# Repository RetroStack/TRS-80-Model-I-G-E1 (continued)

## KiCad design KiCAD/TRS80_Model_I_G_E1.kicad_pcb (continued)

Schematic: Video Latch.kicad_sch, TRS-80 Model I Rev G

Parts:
R39: 4.7k; TRS80_Model_I_R_0.25W
Z7: 74LS74; TRS80_Model_I_DIP14
Z27: 74LS175; TRS80_Model_I_DIP16
Z28: 74LS174; TRS80_Model_I_DIP16
Z30: 74LS02; TRS80_Model_I_DIP14
Z42: 74LS04; TRS80_Model_I_DIP14

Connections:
+5V: R39.2, Z7.14 (VCC), Z27.16 (VCC), Z28.16 (VCC); also elsewhere on the board
/Address Decoder/~VID: Z7.4 (~S); also elsewhere on the board
/Video/Video Counter/HDRV: Z30.8; also elsewhere on the board
/Video/Video Counter/L3: Z27.12 (D2); also elsewhere on the board
/Video/Video Counter/VDRV: Z30.9; also elsewhere on the board
/Video/Video Counter/~LATCH: Z7.3 (C), Z27.9 (Cp), Z28.9 (Cp); also elsewhere on the board
/Video/Video Generator/GRAPHICS: Z27.3 (~Q0); also elsewhere on the board
/Video/Video Generator/LB0: Z28.15 (Q5); also elsewhere on the board
/Video/Video Generator/LB1: Z28.12 (Q4); also elsewhere on the board
/Video/Video Generator/LB2: Z28.2 (Q0); also elsewhere on the board
/Video/Video Generator/LB3: Z28.7 (Q2); also elsewhere on the board
/Video/Video Generator/LB4: Z28.5 (Q1); also elsewhere on the board
/Video/Video Generator/LB5: Z28.10 (Q3); also elsewhere on the board
/Video/Video Generator/LB6: Z27.15 (Q3); also elsewhere on the board
/Video/Video Generator/~BLANK: Z27.7 (Q1); also elsewhere on the board
/Video/Video Generator/~CHARGAP: Z27.11 (~Q2); also elsewhere on the board
/Video/Video Generator/~GRAPHICS: Z27.2 (Q0); also elsewhere on the board
/Video/Video Latch/VD0: Z28.14 (D5); also elsewhere on the board
/Video/Video Latch/VD1: Z28.13 (D4); also elsewhere on the board
/Video/Video Latch/VD2: Z28.3 (D0); also elsewhere on the board
/Video/Video Latch/VD3: Z28.6 (D2); also elsewhere on the board
/Video/Video Latch/VD4: Z28.4 (D1); also elsewhere on the board
/Video/Video Latch/VD5: Z28.11 (D3); also elsewhere on the board
/Video/Video Latch/VD6: Z27.13 (D3); also elsewhere on the board
/Video/Video Latch/VD7: Z42.13; also elsewhere on the board
/Video/Video Latch/~VCLR: Z7.6 (~Q), Z27.1 (~Mr), Z28.1 (~Mr)
GND: Z7.2 (D), Z7.7 (GND), Z7.10 (~S), Z7.11 (C), Z7.12 (D), Z7.13 (~R), Z27.8 (GND), Z28.8 (GND); also elsewhere on the board
unnamed: R39.1, Z7.1 (~R)
unnamed: Z27.4 (D0), Z42.12
unnamed: Z27.5 (D1), Z30.10

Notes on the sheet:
CHARGAP
GRAPHICS
Clear when CPU drives
~{BLANK}
~{GRAPHICS}

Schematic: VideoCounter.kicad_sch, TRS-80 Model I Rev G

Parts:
R63: 4.7k; TRS80_Model_I_R_0.25W
Z12, Z32, Z50, Z65: 74LS93; TRS80_Model_I_DIP14
Z24: 74LS132; TRS80_Model_I_DIP14
Z43: 74LS157; TRS80_Model_I_DIP16
Z58: 74LS92; TRS80_Model_I_DIP14
Z66: 74LS11; TRS80_Model_I_DIP14
Z70: 74LS74; TRS80_Model_I_DIP14

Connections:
+5V: R63.1, Z12.5 (VCC), Z32.5 (VCC), Z43.16 (VCC), Z50.5 (VCC), Z58.5 (VCC), Z65.5 (VCC), Z66.14 (VCC); also elsewhere on the board
/CPU/CLK: Z43.3 (I1a), Z70.11 (C); also elsewhere on the board
/CPU/HI: Z70.10 (~S); also elsewhere on the board
/CPU/~CLK_EN: Z58.6 (R0(1)), Z58.7 (R0(2)); also elsewhere on the board
/Cassette Interface/MODESEL: Z43.1 (S); also elsewhere on the board
/Video/Video Access Multiplexer/C0: Z43.7 (Zb); also elsewhere on the board
/Video/Video Access Multiplexer/C1: Z65.9 (Q1); also elsewhere on the board
/Video/Video Access Multiplexer/C2: Z50.14 (CP0), Z65.8 (Q2); also elsewhere on the board
/Video/Video Access Multiplexer/C3: Z50.1 (CP1..3), Z50.12 (Q0); also elsewhere on the board
/Video/Video Access Multiplexer/C4: Z50.9 (Q1), Z66.3; also elsewhere on the board
/Video/Video Access Multiplexer/C5: Z50.8 (Q2), Z66.5; also elsewhere on the board
/Video/Video Access Multiplexer/R0: Z32.14 (CP0), Z65.12 (Q0); also elsewhere on the board
/Video/Video Access Multiplexer/R1: Z32.1 (CP1..3), Z32.12 (Q0), Z66.13; also elsewhere on the board
/Video/Video Access Multiplexer/R2: Z32.9 (Q1), Z66.2; also elsewhere on the board
/Video/Video Access Multiplexer/R3: Z32.8 (Q2); also elsewhere on the board
/Video/Video Counter/HDRV: Z12.14 (CP0), Z50.11 (Q3), Z66.4; also elsewhere on the board
/Video/Video Counter/L0: Z12.1 (CP1..3), Z12.12 (Q0); also elsewhere on the board
/Video/Video Counter/L1: Z12.9 (Q1); also elsewhere on the board
/Video/Video Counter/L2: Z12.8 (Q2), Z66.9, Z66.10; also elsewhere on the board
/Video/Video Counter/L3: Z12.11 (Q3), Z65.14 (CP0), Z66.11; also elsewhere on the board
/Video/Video Counter/SHIFT: Z43.4 (Za), Z58.14 (CP0); also elsewhere on the board
/Video/Video Counter/VDRV: Z32.11 (Q3), Z66.1; also elsewhere on the board
/Video/Video Counter/~LATCH: Z24.3; also elsewhere on the board
GND: Z12.10 (GND), Z32.10 (GND), Z43.5 (I0b), Z43.8 (GND), Z43.15 (E), Z50.10 (GND), Z58.10 (GND), Z65.2 (R0(1)), Z65.3 (R0(2)), Z65.10 (GND), Z66.7 (GND); also elsewhere on the board
unnamed: Z12.2 (R0(1)), Z12.3 (R0(2)), Z66.8
unnamed: Z32.2 (R0(1)), Z32.3 (R0(2)), Z66.12
unnamed: Z43.2 (I0a), Z70.9 (Q)
unnamed: Z24.2, Z43.11 (I0c), Z58.9 (Q2)
unnamed: Z43.6 (I1b), Z43.10 (I1c), Z58.8 (Q3)
unnamed: Z43.9 (Zc), Z65.1 (CP1..3)
unnamed: Z50.2 (R0(1)), Z50.3 (R0(2)), Z66.6
unnamed: Z24.1, Z58.1 (CP1..3), Z58.12 (Q0)
unnamed: Z70.8 (~Q), Z70.12 (D)
unnamed: R63.2, Z70.13 (~R)

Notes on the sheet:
BIT 1
7.92 kHz
CLK/2
660 Hz
CP0/2
1.98 kHz
60 Hz
887.042 kHz
1.32 kHz
Character line counter
82.5 Hz
27.72 kHz
Mode Selector
CP0/11
3.96 kHz
110.88 kHz
CP1/4
221.76 kHz
55.44 kHz
15.84 kHz
CP0/6
CP0/12
BIT 3
330 Hz
Column counter
Row counter
10.6445 MHz
5.322 MHz
443.52 kHz
CP0/14
165 Hz
Every 6th count

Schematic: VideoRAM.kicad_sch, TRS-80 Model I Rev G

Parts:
Z30: 74LS02; TRS80_Model_I_DIP14
Z44, Z60: 74LS367; TRS80_Model_I_DIP16
Z45, Z46, Z47, Z48, Z61, Z62, Z63: 2102; DIP-16_W7.62mm

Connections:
+5V: Z45.10 (VCC), Z46.10 (VCC), Z47.10 (VCC), Z48.10 (VCC), Z60.16 (VCC), Z61.10 (VCC), Z62.10 (VCC), Z63.10 (VCC); also elsewhere on the board
/D0: Z44.7, Z48.11 (IN); also elsewhere on the board
/D1: Z44.5, Z47.11 (IN); also elsewhere on the board
/D2: Z44.3, Z46.11 (IN); also elsewhere on the board
/D3: Z44.9, Z45.11 (IN); also elsewhere on the board
/D4: Z60.9, Z61.11 (IN); also elsewhere on the board
/D5: Z60.7, Z62.11 (IN); also elsewhere on the board
/D6: Z60.5; also elsewhere on the board
/D7: Z60.3, Z63.11 (IN); also elsewhere on the board
/Video/Video Access Multiplexer/VA0: Z45.8 (A0), Z46.8 (A0), Z47.8 (A0), Z48.8 (A0), Z61.8 (A0), Z62.8 (A0), Z63.8 (A0); also elsewhere on the board
/Video/Video Access Multiplexer/VA1: Z45.4 (A1), Z46.4 (A1), Z47.4 (A1), Z48.4 (A1), Z61.4 (A1), Z62.4 (A1), Z63.4 (A1); also elsewhere on the board
/Video/Video Access Multiplexer/VA2: Z45.5 (A2), Z46.5 (A2), Z47.5 (A2), Z48.5 (A2), Z61.5 (A2), Z62.5 (A2), Z63.5 (A2); also elsewhere on the board
/Video/Video Access Multiplexer/VA3: Z45.6 (A3), Z46.6 (A3), Z47.6 (A3), Z48.6 (A3), Z61.6 (A3), Z62.6 (A3), Z63.6 (A3); also elsewhere on the board
/Video/Video Access Multiplexer/VA4: Z45.7 (A4), Z46.7 (A4), Z47.7 (A4), Z48.7 (A4), Z61.7 (A4), Z62.7 (A4), Z63.7 (A4); also elsewhere on the board
/Video/Video Access Multiplexer/VA5: Z45.2 (A5), Z46.2 (A5), Z47.2 (A5), Z48.2 (A5), Z61.2 (A5), Z62.2 (A5), Z63.2 (A5); also elsewhere on the board
/Video/Video Access Multiplexer/VA6: Z45.1 (A6), Z46.1 (A6), Z47.1 (A6), Z48.1 (A6), Z61.1 (A6), Z62.1 (A6), Z63.1 (A6); also elsewhere on the board
/Video/Video Access Multiplexer/VA7: Z45.16 (A7), Z46.16 (A7), Z47.16 (A7), Z48.16 (A7), Z61.16 (A7), Z62.16 (A7), Z63.16 (A7); also elsewhere on the board
/Video/Video Access Multiplexer/VA8: Z45.15 (A8), Z46.15 (A8), Z47.15 (A8), Z48.15 (A8), Z61.15 (A8), Z62.15 (A8), Z63.15 (A8); also elsewhere on the board
/Video/Video Access Multiplexer/VA9: Z45.14 (A9), Z46.14 (A9), Z47.14 (A9), Z48.14 (A9), Z61.14 (A9), Z62.14 (A9), Z63.14 (A9); also elsewhere on the board
/Video/Video Access Multiplexer/~VRD: Z44.1, Z60.1; also elsewhere on the board
/Video/Video Access Multiplexer/~VWR: Z45.3 (R/~W), Z46.3 (R/~W), Z47.3 (R/~W), Z48.3 (R/~W), Z61.3 (R/~W), Z62.3 (R/~W), Z63.3 (R/~W); also elsewhere on the board
/Video/Video Latch/VD0: Z44.6, Z48.12 (OUT); also elsewhere on the board
/Video/Video Latch/VD1: Z44.4, Z47.12 (OUT); also elsewhere on the board
/Video/Video Latch/VD2: Z44.2, Z46.12 (OUT); also elsewhere on the board
/Video/Video Latch/VD3: Z44.10, Z45.12 (OUT); also elsewhere on the board
/Video/Video Latch/VD4: Z60.10, Z61.12 (OUT); also elsewhere on the board
/Video/Video Latch/VD5: Z30.12, Z60.6, Z62.12 (OUT); also elsewhere on the board
/Video/Video Latch/VD6: Z30.13, Z60.4; also elsewhere on the board
/Video/Video Latch/VD7: Z30.11, Z60.2, Z63.12 (OUT); also elsewhere on the board
GND: Z45.9 (GND), Z45.13 (~CE), Z46.9 (GND), Z46.13 (~CE), Z47.9 (GND), Z47.13 (~CE), Z48.9 (GND), Z48.13 (~CE), Z60.8 (GND), Z60.12, Z60.14, Z60.15, Z61.9 (GND), Z61.13 (~CE), Z62.9 (GND), Z62.13 (~CE), Z63.9 (GND), Z63.13 (~CE); also elsewhere on the board

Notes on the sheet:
Derived BIT 6
BIT 5
BIT 7

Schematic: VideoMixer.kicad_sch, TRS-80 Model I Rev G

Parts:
C2: 10uF 16V; TRS80_Model_I_C_Pol_Radial_5D_2.5P
C7: 0.01uF 24V; TRS80_Model_I_C_Disc_9.5L_4W_6P_Small
J2: Front View; TRS80_Model_I_DIN5
Q1: 2N3904; TRS80_Model_I_Q_Circle_EBC
Q2: 2N3906; TRS80_Model_I_Q_Circle_EBC
R22: 75; TRS80_Model_I_R_0.25W
R23: 120; TRS80_Model_I_R_0.25W
R27: 330; TRS80_Model_I_R_0.25W
R28: 270; TRS80_Model_I_R_0.25W
R29: 1.8k; TRS80_Model_I_R_0.25W
R30: 47; TRS80_Model_I_R_0.25W
Z41: 75452; TRS80_Model_I_DIP8

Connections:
+5V: J2.1, Q2.1 (E), R30.1; also elsewhere on the board
/Video/Video Generator/PIXEL: Z41.6 (2A), Z41.7 (2B); also elsewhere on the board
/Video/Video Mixer/SYNC: R29.1; also elsewhere on the board
GND: C2.2, C7.2, J2.5, R22.2, R27.2; also elsewhere on the board
unnamed: Q1.2 (B), R23.1, R27.1, R28.2
unnamed: C2.1, C7.1, Q1.3 (C), R30.2
unnamed: J2.4, Q1.1 (E), R22.1
unnamed: Q2.2 (B), R29.2
unnamed: Q2.3 (C), R28.1
unnamed: R23.2, Z41.5 (2Y)

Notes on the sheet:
Q2 open, Z41 any => 0V (sync level) Q2 closed, Z41 closed => 1.23V (black level) - R28 with series resistors R23 & R27 Q2 closed, Z41 open => 2.75V (white level) - Only R27 & R28

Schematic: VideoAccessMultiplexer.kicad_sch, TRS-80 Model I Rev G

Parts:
R49: 4.7k; TRS80_Model_I_R_0.25W
Z31, Z49, Z64: 74LS157; TRS80_Model_I_DIP16

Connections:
+5V: R49.1, Z31.16 (VCC), Z49.16 (VCC), Z64.16 (VCC); also elsewhere on the board
/A0: Z64.11 (I0c); also elsewhere on the board
/A1: Z64.2 (I0a); also elsewhere on the board
/A2: Z64.14 (I0d); also elsewhere on the board
/A3: Z64.5 (I0b); also elsewhere on the board
/A4: Z49.11 (I0c); also elsewhere on the board
/A5: Z49.2 (I0a); also elsewhere on the board
/A6: Z31.11 (I0c); also elsewhere on the board
/A7: Z31.14 (I0d); also elsewhere on the board
/A8: Z31.2 (I0a); also elsewhere on the board
/A9: Z31.5 (I0b); also elsewhere on the board
/Address Decoder/~RD: Z49.5 (I0b); also elsewhere on the board
/Address Decoder/~VID: Z31.1 (S), Z49.1 (S), Z64.1 (S); also elsewhere on the board
/CPU Gating/~WR: Z49.14 (I0d); also elsewhere on the board
/Video/Video Access Multiplexer/C0: Z64.10 (I1c); also elsewhere on the board
/Video/Video Access Multiplexer/C1: Z64.3 (I1a); also elsewhere on the board
/Video/Video Access Multiplexer/C2: Z64.13 (I1d); also elsewhere on the board
/Video/Video Access Multiplexer/C3: Z64.6 (I1b); also elsewhere on the board
/Video/Video Access Multiplexer/C4: Z49.10 (I1c); also elsewhere on the board
/Video/Video Access Multiplexer/C5: Z49.3 (I1a); also elsewhere on the board
/Video/Video Access Multiplexer/R0: Z31.10 (I1c); also elsewhere on the board
/Video/Video Access Multiplexer/R1: Z31.13 (I1d); also elsewhere on the board
/Video/Video Access Multiplexer/R2: Z31.3 (I1a); also elsewhere on the board
/Video/Video Access Multiplexer/R3: Z31.6 (I1b); also elsewhere on the board
/Video/Video Access Multiplexer/VA0: Z64.9 (Zc); also elsewhere on the board
/Video/Video Access Multiplexer/VA1: Z64.4 (Za); also elsewhere on the board
/Video/Video Access Multiplexer/VA2: Z64.12 (Zd); also elsewhere on the board
/Video/Video Access Multiplexer/VA3: Z64.7 (Zb); also elsewhere on the board
/Video/Video Access Multiplexer/VA4: Z49.9 (Zc); also elsewhere on the board
/Video/Video Access Multiplexer/VA5: Z49.4 (Za); also elsewhere on the board
/Video/Video Access Multiplexer/VA6: Z31.9 (Zc); also elsewhere on the board
/Video/Video Access Multiplexer/VA7: Z31.12 (Zd); also elsewhere on the board
/Video/Video Access Multiplexer/VA8: Z31.4 (Za); also elsewhere on the board
/Video/Video Access Multiplexer/VA9: Z31.7 (Zb); also elsewhere on the board
/Video/Video Access Multiplexer/~VRD: Z49.7 (Zb); also elsewhere on the board
/Video/Video Access Multiplexer/~VWR: Z49.12 (Zd); also elsewhere on the board
GND: Z31.8 (GND), Z31.15 (E), Z49.8 (GND), Z49.15 (E), Z64.8 (GND), Z64.15 (E); also elsewhere on the board
unnamed: R49.2, Z49.6 (I1b), Z49.13 (I1d)

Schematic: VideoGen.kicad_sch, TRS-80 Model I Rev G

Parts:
R40: 4.7k; TRS80_Model_I_R_0.25W
Z8: 74LS153; TRS80_Model_I_DIP16
Z9: 74LS04; TRS80_Model_I_DIP14
Z10, Z11: 74LS166; TRS80_Model_I_DIP16
Z26: 74LS20; TRS80_Model_I_DIP14
Z29: MCM6670; DIP-18_W7.62mm
Z30: 74LS02; TRS80_Model_I_DIP14

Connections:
+5V: R40.2, Z8.16 (VCC), Z9.14 (VCC), Z10.16 (VCC), Z11.16 (VCC), Z26.14 (VCC), Z29.18 (VCC); also elsewhere on the board
/Video/Video Counter/L0: Z29.11 (R0); also elsewhere on the board
/Video/Video Counter/L1: Z29.10 (R1); also elsewhere on the board
/Video/Video Counter/L2: Z8.14 (S0), Z29.8 (R2); also elsewhere on the board
/Video/Video Counter/L3: Z8.2 (S1); also elsewhere on the board
/Video/Video Counter/SHIFT: Z9.9; also elsewhere on the board
/Video/Video Counter/~LATCH: Z9.3; also elsewhere on the board
/Video/Video Generator/GRAPHICS: Z26.4; also elsewhere on the board
/Video/Video Generator/LB0: Z8.6 (I0a), Z29.7 (A0); also elsewhere on the board
/Video/Video Generator/LB1: Z8.10 (I0b), Z29.6 (A1); also elsewhere on the board
/Video/Video Generator/LB2: Z8.5 (I1a), Z29.5 (A2); also elsewhere on the board
/Video/Video Generator/LB3: Z8.11 (I1b), Z29.4 (A3); also elsewhere on the board
/Video/Video Generator/LB4: Z8.4 (I2a), Z29.3 (A4); also elsewhere on the board
/Video/Video Generator/LB5: Z8.12 (I2b), Z29.2 (A5); also elsewhere on the board
/Video/Video Generator/LB6: Z29.1 (A6); also elsewhere on the board
/Video/Video Generator/PIXEL: Z30.1; also elsewhere on the board
/Video/Video Generator/~BLANK: Z26.1, Z26.2, Z26.9; also elsewhere on the board
/Video/Video Generator/~CHARGAP: Z26.12; also elsewhere on the board
/Video/Video Generator/~GRAPHICS: Z26.10; also elsewhere on the board
GND: Z8.1 (Ea), Z8.8 (GND), Z8.15 (Eb), Z9.1, Z9.5, Z9.7 (GND), Z9.11, Z9.13, Z10.1 (Ds), Z10.2 (A), Z10.3 (B), Z10.6 (CE), Z10.8 (GND), Z10.14 (H), Z11.1 (Ds), Z11.2 (A), Z11.3 (B), Z11.6 (CE), Z11.8 (GND), Z26.7 (GND), Z29.9 (GND), Z29.17 (~CS); also elsewhere on the board
unnamed: Z10.4 (C), Z29.12 (D0)
unnamed: Z9.8, Z10.7 (Clk), Z11.7 (Clk)
unnamed: R40.1, Z10.9 (Clr), Z11.9 (Clr)
unnamed: Z10.5 (D), Z29.13 (D1)
unnamed: Z10.10 (E), Z29.14 (D2)
unnamed: Z10.11 (F), Z29.15 (D3)
unnamed: Z10.12 (G), Z29.16 (D4)
unnamed: Z10.15 (PE), Z26.8
unnamed: Z10.13 (Qh), Z30.3
unnamed: Z8.9 (Zb), Z11.4 (C), Z11.5 (D), Z11.10 (E)
unnamed: Z8.7 (Za), Z11.11 (F), Z11.12 (G), Z11.14 (H)
unnamed: Z11.15 (PE), Z26.6
unnamed: Z11.13 (Qh), Z30.2
unnamed: Z9.4, Z26.5, Z26.13

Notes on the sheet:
ASCII
Character Generators: - Motorola 3108001 (floating "a") - Motorola MCM6670 (fixed floating "a") - Motorola 8046673 SCM37530 (latest)
SHIFT/~{LOAD}
LATCH
Right
GRAPHICS PIXEL
Left
Character Generator
GRAPHICS
~{SHIFT}
ASCII PIXEL
Inversed Clock (delays clock)

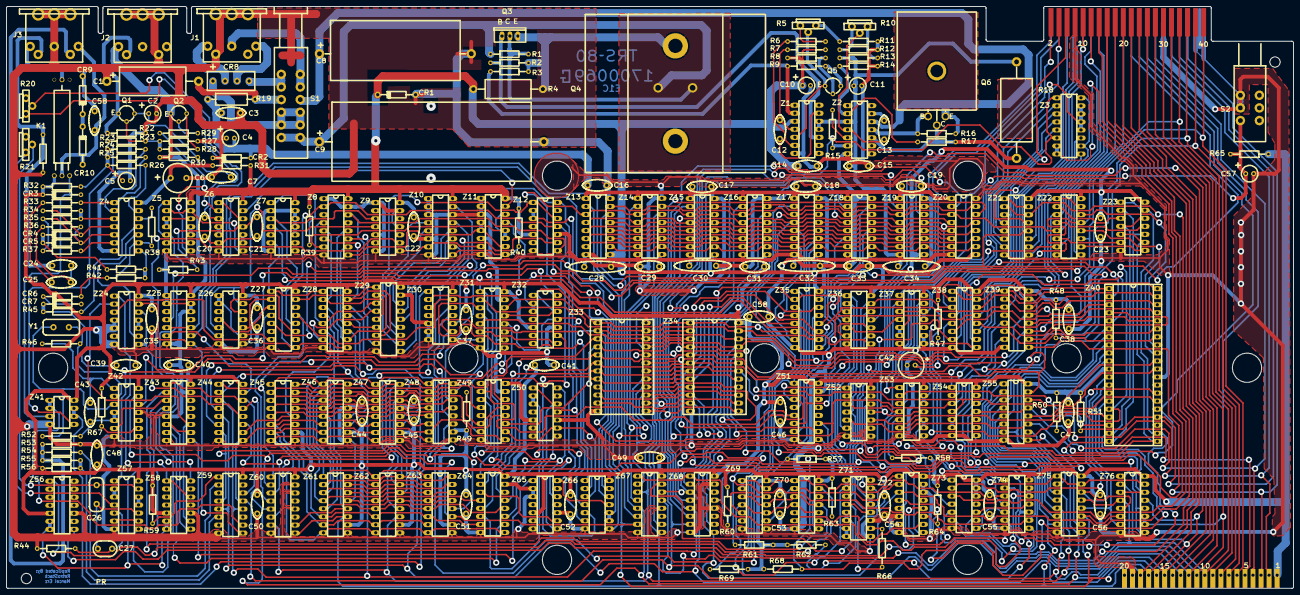
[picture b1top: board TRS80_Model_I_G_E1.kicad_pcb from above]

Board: 2 copper layers, 407.0 x 184.0 mm, 230 parts (0 on the bottom side), 311 nets.

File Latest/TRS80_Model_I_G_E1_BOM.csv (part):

SOURCE PCB REFERENCE,QTY,VALUE,COMPONENT NAME,COMPONENT DESCRIPTION,COMMENT,EACH,TOTAL,SOURCE,SOURCE LINK
C1,1,220uF 16V,C_Polarized,Polarized capacitor,,$1.48,$1.48,Mouser,https://www.mouser.com/ProductDetail/598-227TTA050M
"C2, C4, C5, C10, C11, C57",6,10uF 16V,C_Polarized,Polarized capacitor,C57 is located at the reset switch,$0.29,$1.74,Mouser,https://www.mouser.com/ProductDetail/598-106RMR050M
C6,1,100uF 16V,C_Polarized,Polarized capacitor,,$0.37,$0.37,Mouser,https://www.mouser.com/ProductDetail/647-UVZ1J101MPD
C8,1,2200uF 35V,C_Polarized,Polarized capacitor,,$5.31,$5.31,Mouser,https://www.mouser.com/ProductDetail/598-228TTA063M
C9,1,10000uF 16V,C_Polarized,Polarized capacitor,,$7.87,$7.87,Mouser,https://www.mouser.com/ProductDetail/598-109TTA025M
C42,1,22uF 16V,C_Polarized,Polarized capacitor,,$0.10,$0.10,Mouser,https://www.mouser.com/ProductDetail/710-860010372002
"C12, C13",2,470pF,C (471),Unpolarized capacitor,,$0.23,$0.46,Mouser,https://www.mouser.com/ProductDetail/594-D471K20Y5PH6UJ5R
"C3, C7, C14, C15",4,0.01uF 24V,C (103),Unpolarized capacitor,,$0.23,$0.92,Mouser,https://www.mouser.com/ProductDetail/594-D103Z25Z5VF63L6R
"C16, C17, C18, C19, C22, C23, C28, C29, C30, C31, C32, C33, C34, C35, C36, C37, C38, C39, C40, C41, C44, C45, C46, C47, C48, C49, C50, C51, C52, C53, C54, C55, C56, C58",34,0.1uF 25V,C (104),Unpolarized capacitor,"C58 is located to the right of ROM B C58 next to the relay stays empty (!!!)",$0.17,$5.78,Mouser,https://www.mouser.com/ProductDetail/594-K104K10X7RF53L2
C20,1,330pF,C (331),Unpolarized capacitor,,$0.30,$0.30,Mouser,https://www.mouser.com/ProductDetail/594-F331K29Y5RP6UK5R
C21,1,750pF,C (750),Unpolarized capacitor,,$0.37,$0.37,Mouser,https://www.mouser.com/ProductDetail/80-C322C751K3G5TA
"C24, C25",2,220pF,C (221),Unpolarized capacitor,,$0.23,$0.46,Mouser,https://www.mouser.com/ProductDetail/594-D221K20Y5PF63J5R
C43,1,47pF,C (47),Unpolarized capacitor,C43 is located to the right of Z41,$0.40,$0.40,Mouser,https://www.mouser.com/ProductDetail/594-S470K25SL0N63L6R
C26,1,0.047uF,C (47nF),Unpolarized capacitor,,$1.90,$1.90,Mouser,https://www.mouser.com/ProductDetail/594-222236755473
C27,1,0.022uF,C (22nF),Unpolarized capacitor,,$1.34,$1.34,Mouser,https://www.mouser.com/ProductDetail/594-2222-366-45223
CR1,1,1N4735,D_Zener,Zener diode,,$0.25,$0.25,Mouser,https://www.mouser.com/ProductDetail/512-1N4735A
CR2,1,1N5231,D_Zener,Zener diode,,$0.15,$0.15,Mouser,https://www.mouser.com/ProductDetail/512-1N5231B
"CR3, CR4, CR5, CR6, CR7",5,1N4148,D,Diode,,$0.10,$0.50,Mouser,https://www.mouser.com/ProductDetail/512-1N4148
"CR9, CR10",2,1N982,D_Schottky,Schottky diode,Replacement can be lower than 75V,$0.26,$0.52,Mouser,https://www.mouser.com/ProductDetail/78-1N4754A-TAP
CR8,1,MDA202,D_Bridge_+AA-,"Diode bridge, +ve/AC/AC/-ve",Replacement KBP210,$0.61,$0.61,Mouser,https://www.mouser.com/ProductDetail/621-KBP210G
"J1, J2, J3",3,Front View,DIN-5_180degree,5-pin DIN connector (5-pin DIN-5 stereo),,$0.39,$1.16,AliExpress,https://www.aliexpress.us/item/2255801077942335.html
J100,1,Connector,Conn_01x20,"Generic connector, single row, 01x20",,$0.50,$0.50,Mouser,https://www.mouser.com/ProductDetail/649-1012937992002BLF
K1,1,Relay_SPST-NO,TRS80_Model_I_Relay_NO,"Relay SPST, Normally Open, EN50005",Slightly smaller than original,$14.84,$14.84,DigiKey,https://www.digikey.com/en/products/detail/sensata-cynergy3/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
Q1,1,2N3904,2N3904,"0.2A Ic, 40V Vce, Small Signal NPN Transistor, TO-92",,$0.35,$0.35,Mouser,https://www.mouser.com/ProductDetail/512-2N3904BU
"Q2, Q5",2,2N3906,2N3906,"-0.2A Ic, -40V Vce, Small Signal PNP Transistor, TO-92",,$0.28,$0.56,Mouser,https://www.mouser.com/ProductDetail/512-2N3906BU
Q3,1,TIP29A,Q_NPN_BCE,"NPN transistor, base/collector/emitter",,$1.01,$1.01,Mouser,https://www.mouser.com/ProductDetail/863-TIP29AG
Q4,1,2N6594,Q_PNP_BEC,"PNP transistor, base/emitter/collector","Replacement RS2040, MJ2955G",$4.75,$4.75,Mouser,https://www.mouser.com/ProductDetail/863-MJ2955G
Q6,1,MJE34,Q_PNP_BCE,"PNP transistor, base/collector/emitter",Replacement TIP32C,$0.67,$0.67,Mouser,https://www.mouser.com/ProductDetail/511-TIP32C
-,1,,,Q4 Heatsink,,$1.01,$1.01,Mouser,https://www.mouser.com/ProductDetail/532-506007B00
-,1,,,Q6 Heatsink,Smaller than original,$0.30,$0.30,Mouser,https://www.mouser.com/ProductDetail/532-507302B00
R1,1,68,,"Resistor 0.25W (blue, grey, black, gold)",,$0.10,$0.10,Mouser,https://www.mouser.com/ProductDetail/603-CFR-25JB-52-68R
R2,1,2.7k,,"Resistor 0.25W (red, violet, red, gold)",,$0.10,$0.10,Mouser,https://www.mouser.com/ProductDetail/603-CFR-25JR-522K7
R3,1,750,,"Resistor 0.25W (violet, green, brown, gold)",,$0.10,$0.10,Mouser,https://www.mouser.com/ProductDetail/603-CFR-25JB-52-750R
R4,1,0.33,,"Resistor 2W (orange, orange, silver, gold)",,$0.45,$0.45,Mouser,https://www.mouser.com/ProductDetail/603-CFR2WSJT-73-0R33
"R6, R7, R16, R53",4,1.2k,,"Resistor 0.25W (brown, red, red, gold)",,$0.10,$0.40,Mouser,https://www.mouser.com/ProductDetail/603-CFR-25JB-52-1K2
R8,1,100k,,"Resistor 0.25W (brown, black, yellow, gold)",,$0.10,$0.10,Mouser,https://www.mouser.com/ProductDetail/603-CFR-25JB-52-100K
"R9, R11, R12",3,3.3k,,"Resistor 0.25W (orange, orange, red, gold)",,$0.10,$0.30,Mouser,https://www.mouser.com/ProductDetail/603-CFR-25JB-52-3K3
R13,1,2.2k,,"Resistor 0.25W (red, red, red, gold)",,$0.10,$0.10,Mouser,https://www.mouser.com/ProductDetail/603-CFR-25JT-52-2K2
R14,1,12k,,"Resistor 0.25W (brown, red, orange, gold)",,$0.10,$0.10,Mouser,https://www.mouser.com/ProductDetail/603-CFR-25JB-52-12K
R15,1,1.5k,,"Resistor 0.25W (brown, green, red, gold)",,$0.10,$0.10,Mouser,https://www.mouser.com/ProductDetail/603-CFR-25JT-52-1K5
R17,1,2k,,"Resistor 0.25W (red, black, red, gold)",,$0.10,$0.10,Mouser,https://www.mouser.com/ProductDetail/603-CFR-25JB-52-2K
R18,1,5.6,,"Resistor 3W (green, blue, gold, gold)",,$0.57,$0.57,Mouser,https://www.mouser.com/ProductDetail/279-EP3WSS5R6J
"R19, C_R67",2,220,,"Resistor 0.5W (red, red, brown, gold)",C_R67 is located to the left of K1,$0.10,$0.20,Mouser,https://www.mouser.com/ProductDetail/603-CFR-50JB-52-220R
R22,1,75,,"Resistor 0.25W (violet, green, black, gold)",,$0.10,$0.10,Mouser,https://www.mouser.com/ProductDetail/603-CFR-25JB-52-75R
R23,1,120,,"Resistor 0.25W (brown, red, brown, gold)",,$0.10,$0.10,Mouser,https://www.mouser.com/ProductDetail/603-CFR-25JB-52-120R
R24,1,680k,,"Resistor 0.25W (blue, grey, yellow, gold)",,$0.10,$0.10,Mouser,https://www.mouser.com/ProductDetail/603-CFR-25JB-52-680K
R25,1,1.6M,,"Resistor 0.25W (brown, blue, green, gold)",,$0.10,$0.10,Mouser,https://www.mouser.com/ProductDetail/603-CFR-25JB-52-1M6
"R26, R42",2,1M,,"Resistor 0.25W (brown, black, green, gold)",,$0.10,$0.20,Mouser,https://www.mouser.com/ProductDetail/603-CFR-25JT-52-1M
"R27, R64",2,330,,"Resistor 0.25W (orange, orange, brown, gold)",,$0.10,$0.20,Mouser,https://www.mouser.com/ProductDetail/603-CFR-25JB-52-330R
R28,1,270,,"Resistor 0.25W (red, violet, brown, gold)",,$0.10,$0.10,Mouser,https://www.mouser.com/ProductDetail/603-CFR-25JB-52-270R
R29,1,1.8k,,"Resistor 0.25W (brown, grey, red, gold)",,$0.10,$0.10,Mouser,https://www.mouser.com/ProductDetail/603-CFR-25JB-52-1K8
R30,1,47,,"Resistor 0.25W (yellow, violet, black, gold)",,$0.10,$0.10,Mouser,https://www.mouser.com/ProductDetail/603-CFR-25JB-52-47R
R31,1,10,,"Resistor 0.25W (brown, black, black, gold)",,$0.10,$0.10,Mouser,https://www.mouser.com/ProductDetail/603-CFR-25JT-52-10R
"R32, R43, R44, R47, R65",5,10k,,"Resistor 0.25W (brown, black, orange, gold)","R44 is located in the bottom left corner R65 is located at the reset switch",$0.10,$0.50,Mouser,https://www.mouser.com/ProductDetail/603-CFR-25JB-52-10K
"R33, R36",2,360k,,"Resistor 0.25W (orange, blue, yellow, gold)",,$0.10,$0.20,Mouser,https://www.mouser.com/ProductDetail/603-CFR-25JB-52-360K
"R34, R35, R38, R41, R45",5,470k,,"Resistor 0.25W (yellow, violet, yellow, gold)",,$0.10,$0.50,Mouser,https://www.mouser.com/ProductDetail/603-CFR-25JB-52-470K
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
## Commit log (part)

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2023-12-30 Initial Commit with version E1B
2024-01-05 Fix CASSIN Flip-Flop description
2024-01-14 Cleanup, Changelog added & Curiosities photos
2024-01-22 Update LICENSE
2024-01-23 Update BOM
2024-01-24 Optimizations to BOM
2024-02-21 New labels file and updated BOM
2024-02-21 Cleanup BOM, add locations and Resistor colors
2024-03-04 Add assembly guide
2024-03-04 typos
2024-03-04 Add pages as PDF itself
2024-03-04 Reduce image size
2024-03-05 Move Curiosities out of readme
2024-03-05 Remove duplicates
2024-03-15 Removal of 2N6287 from BOM
2024-03-30 Update schematics (correct page flow) and add alternative to Q4 in BOM
2024-11-30 Updated revision to Rev C
2024-12-02 Update for revisions
2024-12-08 Update Gerber files for latest revision
